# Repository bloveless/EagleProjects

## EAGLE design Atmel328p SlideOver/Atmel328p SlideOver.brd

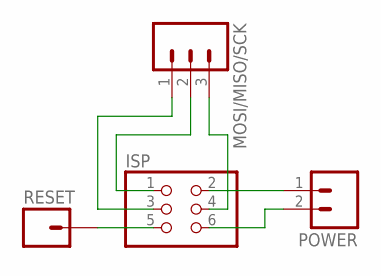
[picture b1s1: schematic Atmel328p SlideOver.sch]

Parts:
ISP: PINHD-2X3; 2X03
MOSI/MISO/SCK: M03PTH; 1X03
POWER: M02PTH; 1X02
RESET: M01PTH; 1X01

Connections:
unnamed: ISP.5, RESET.1
unnamed: ISP.6, POWER.2
unnamed: ISP.3, MOSI/MISO/SCK.1
unnamed: ISP.1, MOSI/MISO/SCK.2
unnamed: ISP.4, MOSI/MISO/SCK.3
POWER: ISP.2, POWER.1

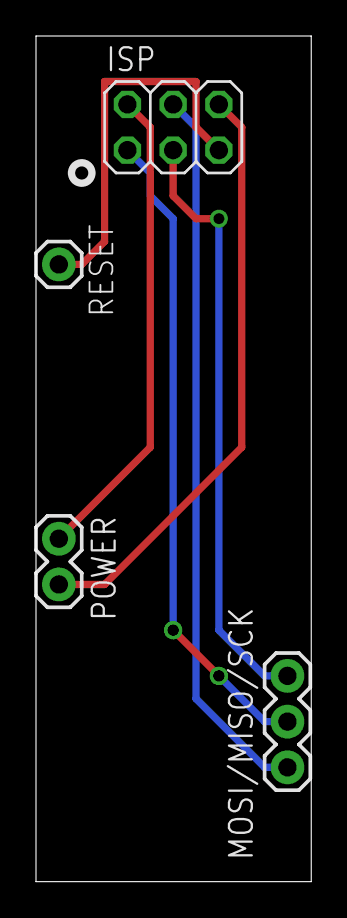
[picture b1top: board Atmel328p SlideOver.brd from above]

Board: 2 copper layers, 15.3 x 47.0 mm, 4 parts (0 on the bottom side), 6 nets.

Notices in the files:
parts and their libraries:
SparkFun-Connectors: Licensing: Creative Commons ShareAlike 4.0 International - https://creativecommons.org/licenses/by-sa/4.0
